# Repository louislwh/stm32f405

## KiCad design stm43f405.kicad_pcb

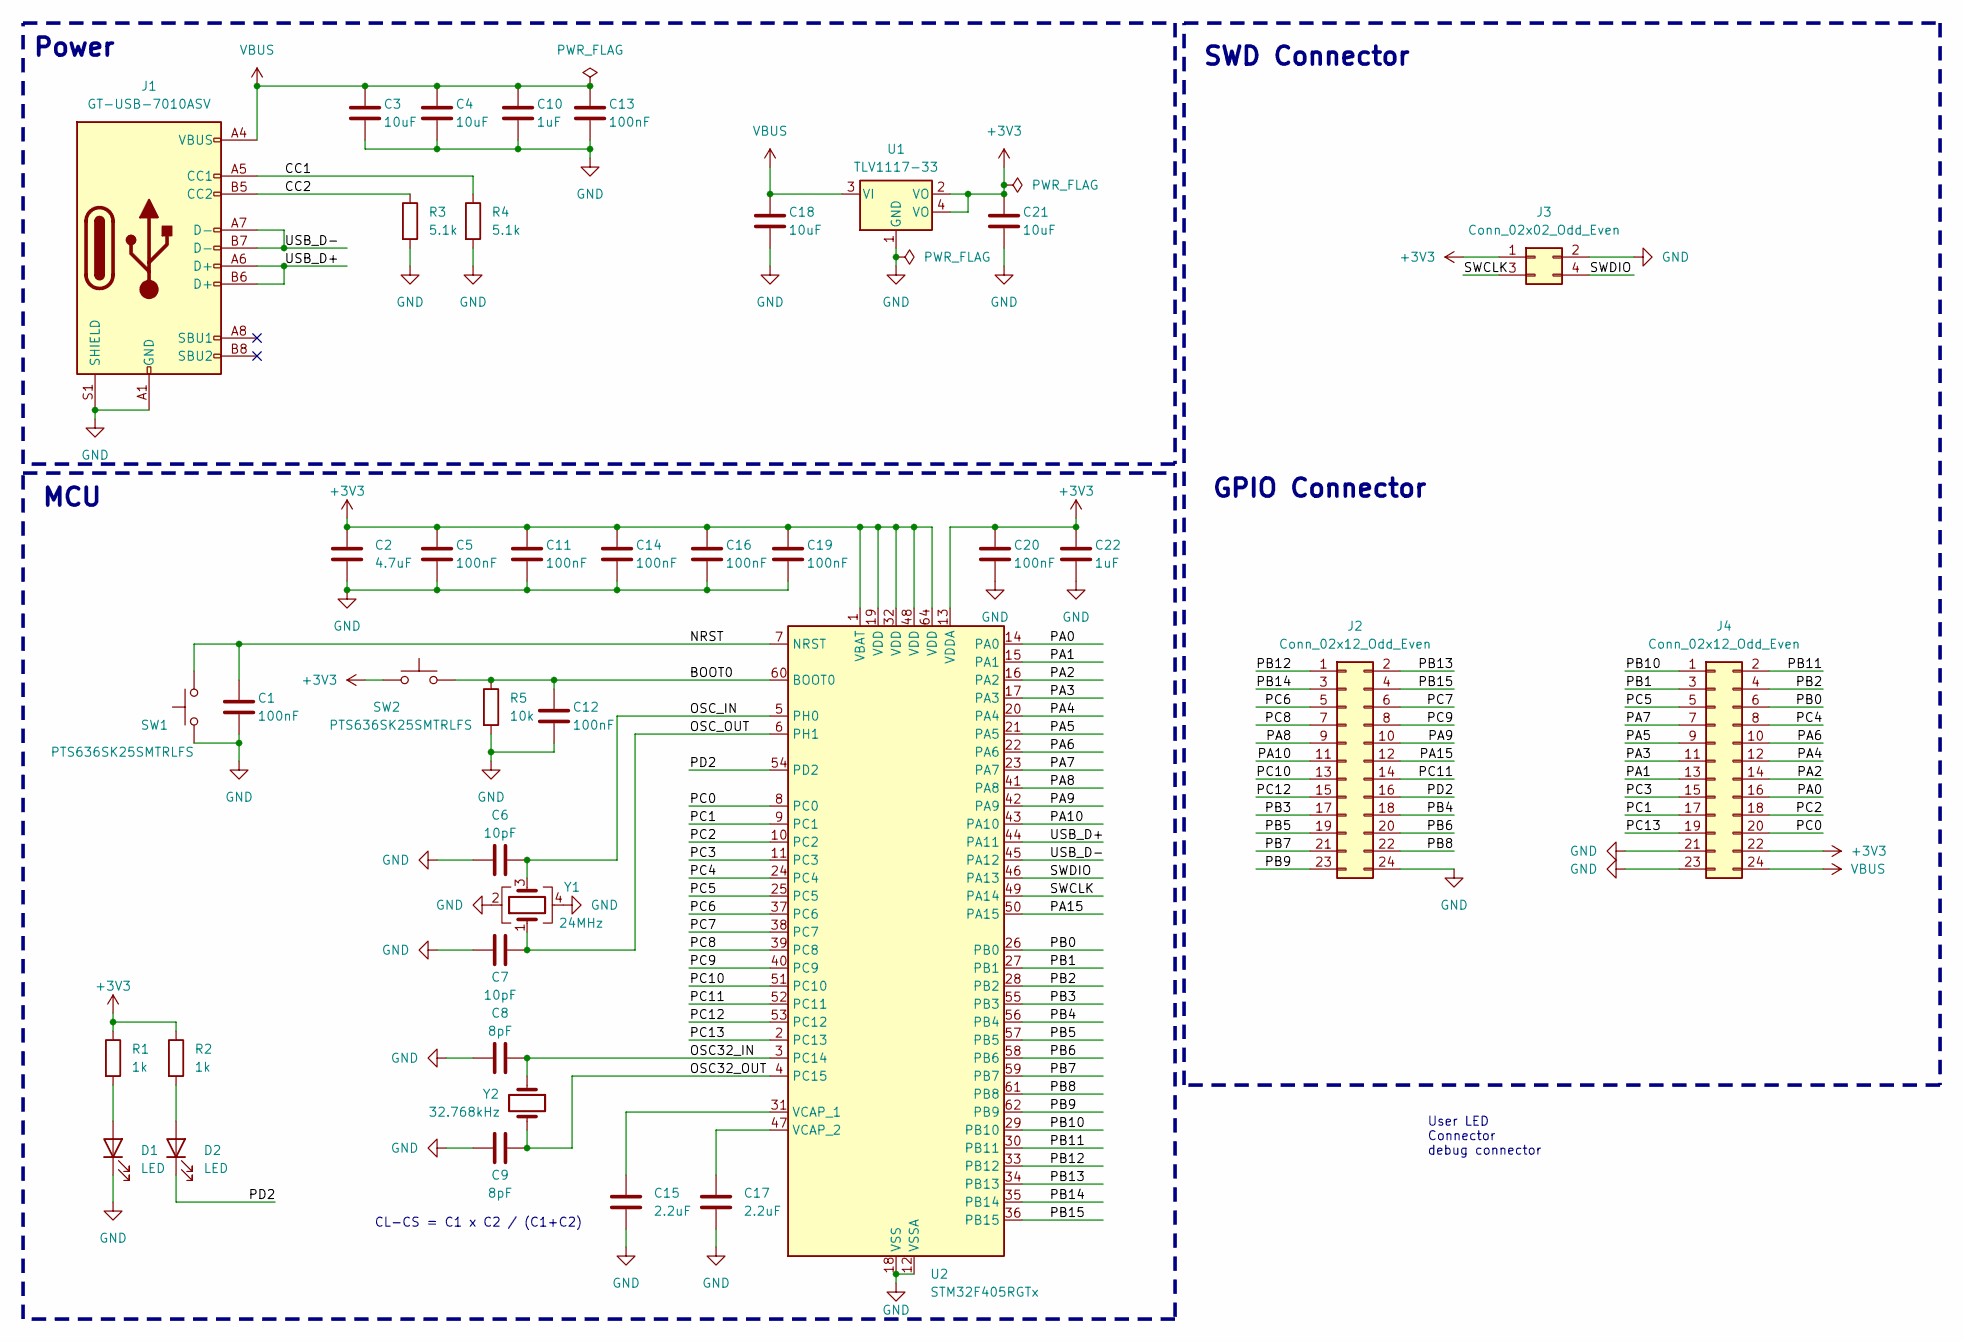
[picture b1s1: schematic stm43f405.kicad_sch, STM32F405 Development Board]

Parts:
C1, C5, C11, C12, C13, C14, C16, C19, C20: 100nF; C_0603_1608Metric; LCSC Part# C14663
C2: 4.7uF; C_0603_1608Metric; LCSC Part# C389010
C3, C4: 10uF; C_0603_1608Metric; LCSC Part# C77044
C6, C7: 10pF; C_0603_1608Metric; LCSC Part# C470847
C8, C9: 8pF; C_0603_1608Metric; LCSC Part# C327316
C10, C22: 1uF; C_0603_1608Metric; LCSC Part# C77386
C15, C17: 2.2uF; C_0603_1608Metric; LCSC Part# C126582
C18, C21: 10uF; CP_EIA-3216-18_Kemet-A; LCSC Part# C110055
D1, D2: LED; LED_0603_1608Metric; LCSC Part# C779453
J1: GT-USB-7010ASV; USB_C_Receptacle_G-Switch_GT-USB-7010ASV; LCSC Part# C2988369
J2, J4: Conn_02x12_Odd_Even; PinHeader_2x12_P2.54mm_Vertical; LCSC Part# C2935922
J3: Conn_02x02_Odd_Even; PinHeader_2x02_P2.54mm_Vertical_SMD; LCSC Part# C5160776
R1, R2: 1k; R_0603_1608Metric; LCSC Part# C22548
R3, R4: 5.1k; R_0603_1608Metric; LCSC Part# C144594
R5: 10k; R_0603_1608Metric; LCSC Part# C98220
SW1, SW2: PTS636SK25SMTRLFS; SW_Tactile_SPST_NO_Straight_CK_PTS636Sx25SMTRLFS; LCSC Part# C2689642
U1: TLV1117-33; SOT-223; LCSC Part# C37359
U2: STM32F405RGTx; LQFP-64_10x10mm_P0.5mm; LCSC Part# C15742
Y1: 24MHz; Crystal_SMD_2520-4Pin_2.5x2.0mm; LCSC Part# C2901725
Y2: 32.768kHz; Crystal_SMD_MicroCrystal_CC8V-T1A-2Pin_2.0x1.2mm_HandSolder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; LCSC Part# C5142652

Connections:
+3V3: C2.1, C5.1, C11.1, C14.1, C16.1, C19.1, C20.1, C21.1, C22.1, J3.1, J4.22, R1.1, R2.1, SW2.1, U1.2 (VO), U1.4 (VO), U2.1 (VBAT), U2.13 (VDDA), U2.19 (VDD), U2.32 (VDD), U2.48 (VDD), U2.64 (VDD)
/BOOT0: C12.1, R5.1, SW2.2, U2.60 (BOOT0)
/CC1: J1.A5 (CC1), R4.1
/CC2: J1.B5 (CC2), R3.1
/NRST: C1.1, SW1.2, U2.7 (NRST)
/OSC32_IN: C8.2, U2.3 (PC14), Y2.1
/OSC32_OUT: C9.2, U2.4 (PC15), Y2.2
/OSC_IN: C6.2, U2.5 (PH0), Y1.3
/OSC_OUT: C7.2, U2.6 (PH1), Y1.1
/PA0: J4.16, U2.14 (PA0)
/PA1: J4.13, U2.15 (PA1)
/PA2: J4.14, U2.16 (PA2)
/PA3: J4.11, U2.17 (PA3)
/PA4: J4.12, U2.20 (PA4)
/PA5: J4.9, U2.21 (PA5)
/PA6: J4.10, U2.22 (PA6)
/PA7: J4.7, U2.23 (PA7)
/PA8: J2.9, U2.41 (PA8)
/PA9: J2.10, U2.42 (PA9)
/PA10: J2.11, U2.43 (PA10)
/PA15: J2.12, U2.50 (PA15)
/PB0: J4.6, U2.26 (PB0)
/PB1: J4.3, U2.27 (PB1)
/PB2: J4.4, U2.28 (PB2)
/PB3: J2.17, U2.55 (PB3)
/PB4: J2.18, U2.56 (PB4)
/PB5: J2.19, U2.57 (PB5)
/PB6: J2.20, U2.58 (PB6)
/PB7: J2.21, U2.59 (PB7)
/PB8: J2.22, U2.61 (PB8)
/PB9: J2.23, U2.62 (PB9)
/PB10: J4.1, U2.29 (PB10)
/PB11: J4.2, U2.30 (PB11)
/PB12: J2.1, U2.33 (PB12)
/PB13: J2.2, U2.34 (PB13)
/PB14: J2.3, U2.35 (PB14)
/PB15: J2.4, U2.36 (PB15)
/PC0: J4.20, U2.8 (PC0)
/PC1: J4.17, U2.9 (PC1)
/PC2: J4.18, U2.10 (PC2)
/PC3: J4.15, U2.11 (PC3)
/PC4: J4.8, U2.24 (PC4)
/PC5: J4.5, U2.25 (PC5)
/PC6: J2.5, U2.37 (PC6)
/PC7: J2.6, U2.38 (PC7)
/PC8: J2.7, U2.39 (PC8)
/PC9: J2.8, U2.40 (PC9)
/PC10: J2.13, U2.51 (PC10)
/PC11: J2.14, U2.52 (PC11)
/PC12: J2.15, U2.53 (PC12)
/PC13: J4.19, U2.2 (PC13)
/PD2: D2.1 (K), J2.16, U2.54 (PD2)
/SWCLK: J3.3, U2.49 (PA14)
/SWDIO: J3.4, U2.46 (PA13)
/USB_D+: J1.A6 (D+), J1.B6 (D+), U2.44 (PA11)
/USB_D-: J1.A7 (D-), J1.B7 (D-), U2.45 (PA12)
GND: C1.2, C2.2, C3.2, C4.2, C5.2, C6.1, C7.1, C8.1, C9.1, C10.2, C11.2, C12.2, C13.2, C14.2, C15.2, C16.2, C17.2, C18.2, C19.2, C20.2, C21.2, C22.2, D1.1 (K), J1.A1 (GND), J1.A12 (GND), J1.B1 (GND), J1.B12 (GND), J1.S1 (SHIELD), J2.24, J3.2, J4.21, J4.23, R3.2, R4.2, R5.2, SW1.1, U1.1 (GND), U2.12 (VSSA), U2.18 (VSS), U2.63 (VSS), Y1.2, Y1.4
unnamed: D1.2 (A), R1.2
unnamed: D2.2 (A), R2.2
unnamed: C15.1, U2.31 (VCAP_1)
unnamed: C17.1, U2.47 (VCAP_2)
VBUS: C3.1, C4.1, C10.1, C13.1, C18.1, J1.A4 (VBUS), J1.A9 (VBUS), J1.B4 (VBUS), J1.B9 (VBUS), J4.24, U1.3 (VI)

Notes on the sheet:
Power
CL-CS = C1 x C2 / (C1+C2)
GPIO Connector
User LED Connector debug connector
SWD Connector
MCU

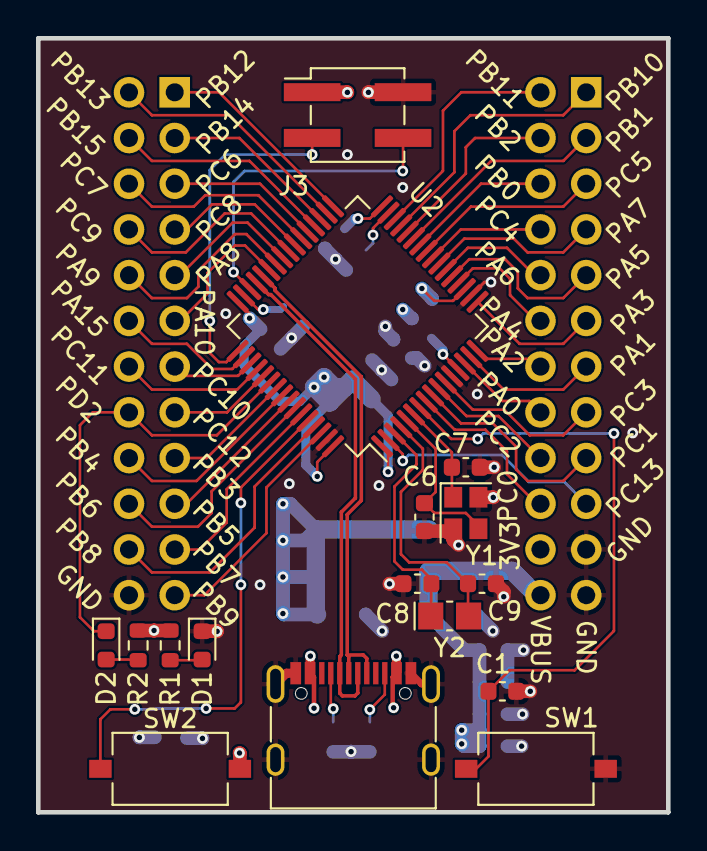
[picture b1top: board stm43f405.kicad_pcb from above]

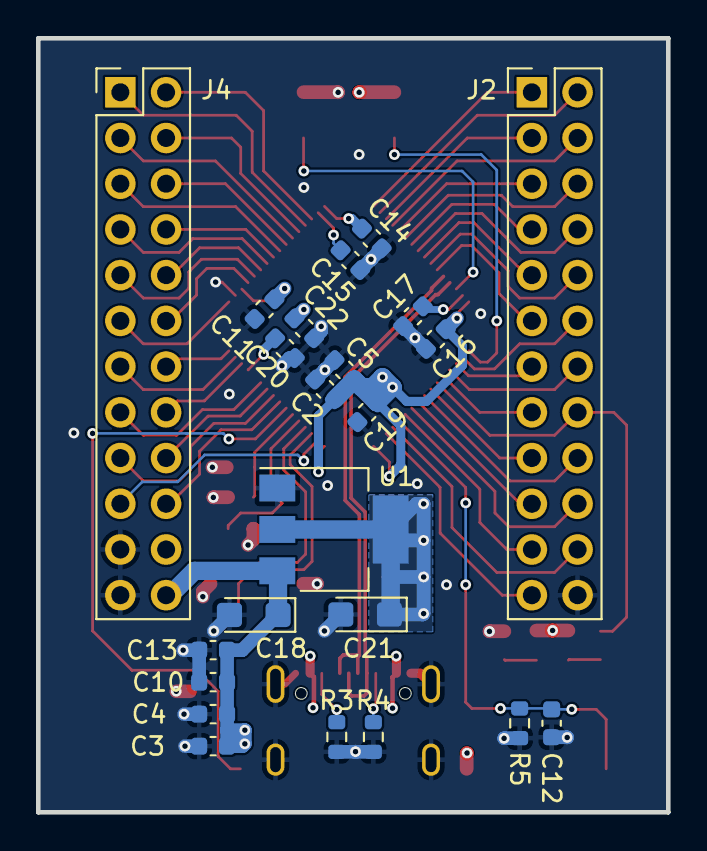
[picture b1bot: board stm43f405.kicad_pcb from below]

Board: 4 copper layers, 35.0 x 43.0 mm, 39 parts (23 on the bottom side), 62 nets.

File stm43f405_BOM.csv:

Reference,Value,Footprint,LCSC Part#
"C1, C5, C11, C12, C13, C14, C16, C19, C20",100nF,Capacitor_SMD:C_0603_1608Metric,C14663
C2,4.7uF,Capacitor_SMD:C_0603_1608Metric,C389010
"C3, C4",10uF,Capacitor_SMD:C_0603_1608Metric,C77044
"C6, C7",10pF,Capacitor_SMD:C_0603_1608Metric,C470847
"C8, C9",8pF,Capacitor_SMD:C_0603_1608Metric,C327316
"C10, C22",1uF,Capacitor_SMD:C_0603_1608Metric,C77386
"C15, C17",2.2uF,Capacitor_SMD:C_0603_1608Metric,C126582
"C18, C21",10uF,Capacitor_Tantalum_SMD:CP_EIA-3216-18_Kemet-A,C110055
"D1, D2",LED,LED_SMD:LED_0603_1608Metric,C779453
J1,GT-USB-7010ASV,Connector_USB:USB_C_Receptacle_G-Switch_GT-USB-7010ASV,C2988369
"J2, J4",Conn_02x12_Odd_Even,Connector_PinHeader_2.54mm:PinHeader_2x12_P2.54mm_Vertical,C2935922
J3,Conn_02x02_Odd_Even,Connector_PinHeader_2.54mm:PinHeader_2x02_P2.54mm_Vertical_SMD,C5160776
"R1, R2",1k,Resistor_SMD:R_0603_1608Metric,C22548
"R3, R4",5.1k,Resistor_SMD:R_0603_1608Metric,C144594
R5,10k,Resistor_SMD:R_0603_1608Metric,C98220
"SW1, SW2",PTS636SK25SMTRLFS,Button_Switch_SMD:SW_Tactile_SPST_NO_Straight_CK_PTS636Sx25SMTRLFS,C2689642
U1,TLV1117-33,Package_TO_SOT_SMD:SOT-223,C37359
U2,STM32F405RGTx,Package_QFP:LQFP-64_10x10mm_P0.5mm,C15742
Y1,24MHz,Crystal:Crystal_SMD_2520-4Pin_2.5x2.0mm,C2901725
Y2,32.768kHz,Crystal:Crystal_SMD_MicroCrystal_CC8V-T1A-2Pin_2.0x1.2mm_HandSoldering,C5142652
